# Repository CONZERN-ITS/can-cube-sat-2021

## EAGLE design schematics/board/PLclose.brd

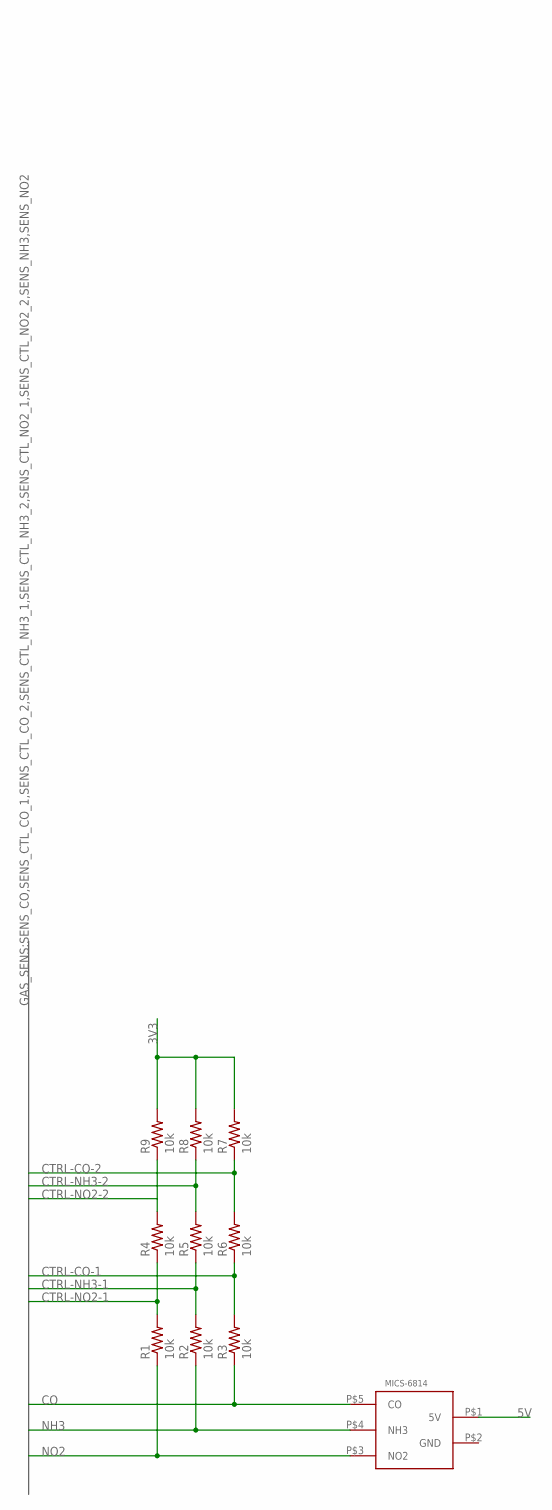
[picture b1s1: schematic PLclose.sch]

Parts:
MICS-6814: MICS-6814
R1, R2, R3, R4, R5, R6, R7, R8, R9: 10k; R0603

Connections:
3V3: R7.2, R8.2, R9.2
5V: MICS-6814.P$1 (5V)
CO: MICS-6814.P$5 (CO), R3.1
CTRL-CO-1: R3.2, R6.1
CTRL-CO-2: R6.2, R7.1
CTRL-NH3-1: R2.2, R5.1
CTRL-NH3-2: R5.2, R8.1
CTRL-NO2-1: R1.2, R4.1
CTRL-NO2-2: R4.2, R9.1
NH3: MICS-6814.P$4 (NH3), R2.1
NO2: MICS-6814.P$3 (NO2), R1.1

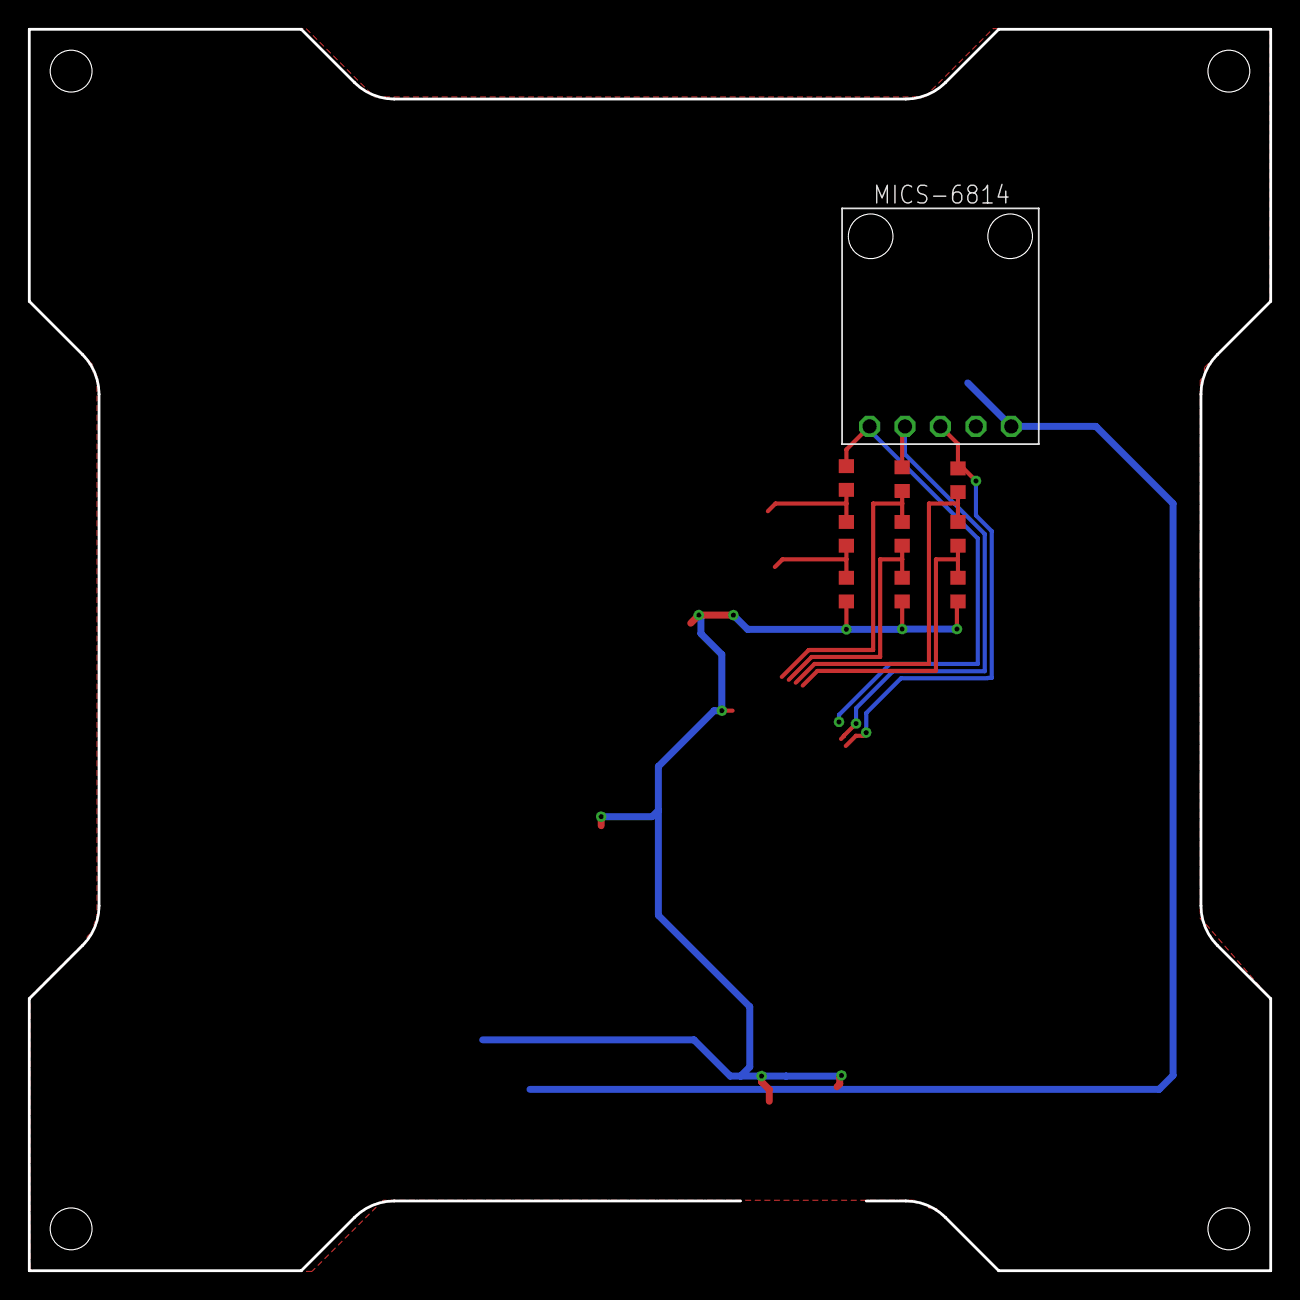
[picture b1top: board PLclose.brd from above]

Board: 2 copper layers, 89.0 x 89.0 mm, 10 parts (0 on the bottom side), 10 nets.

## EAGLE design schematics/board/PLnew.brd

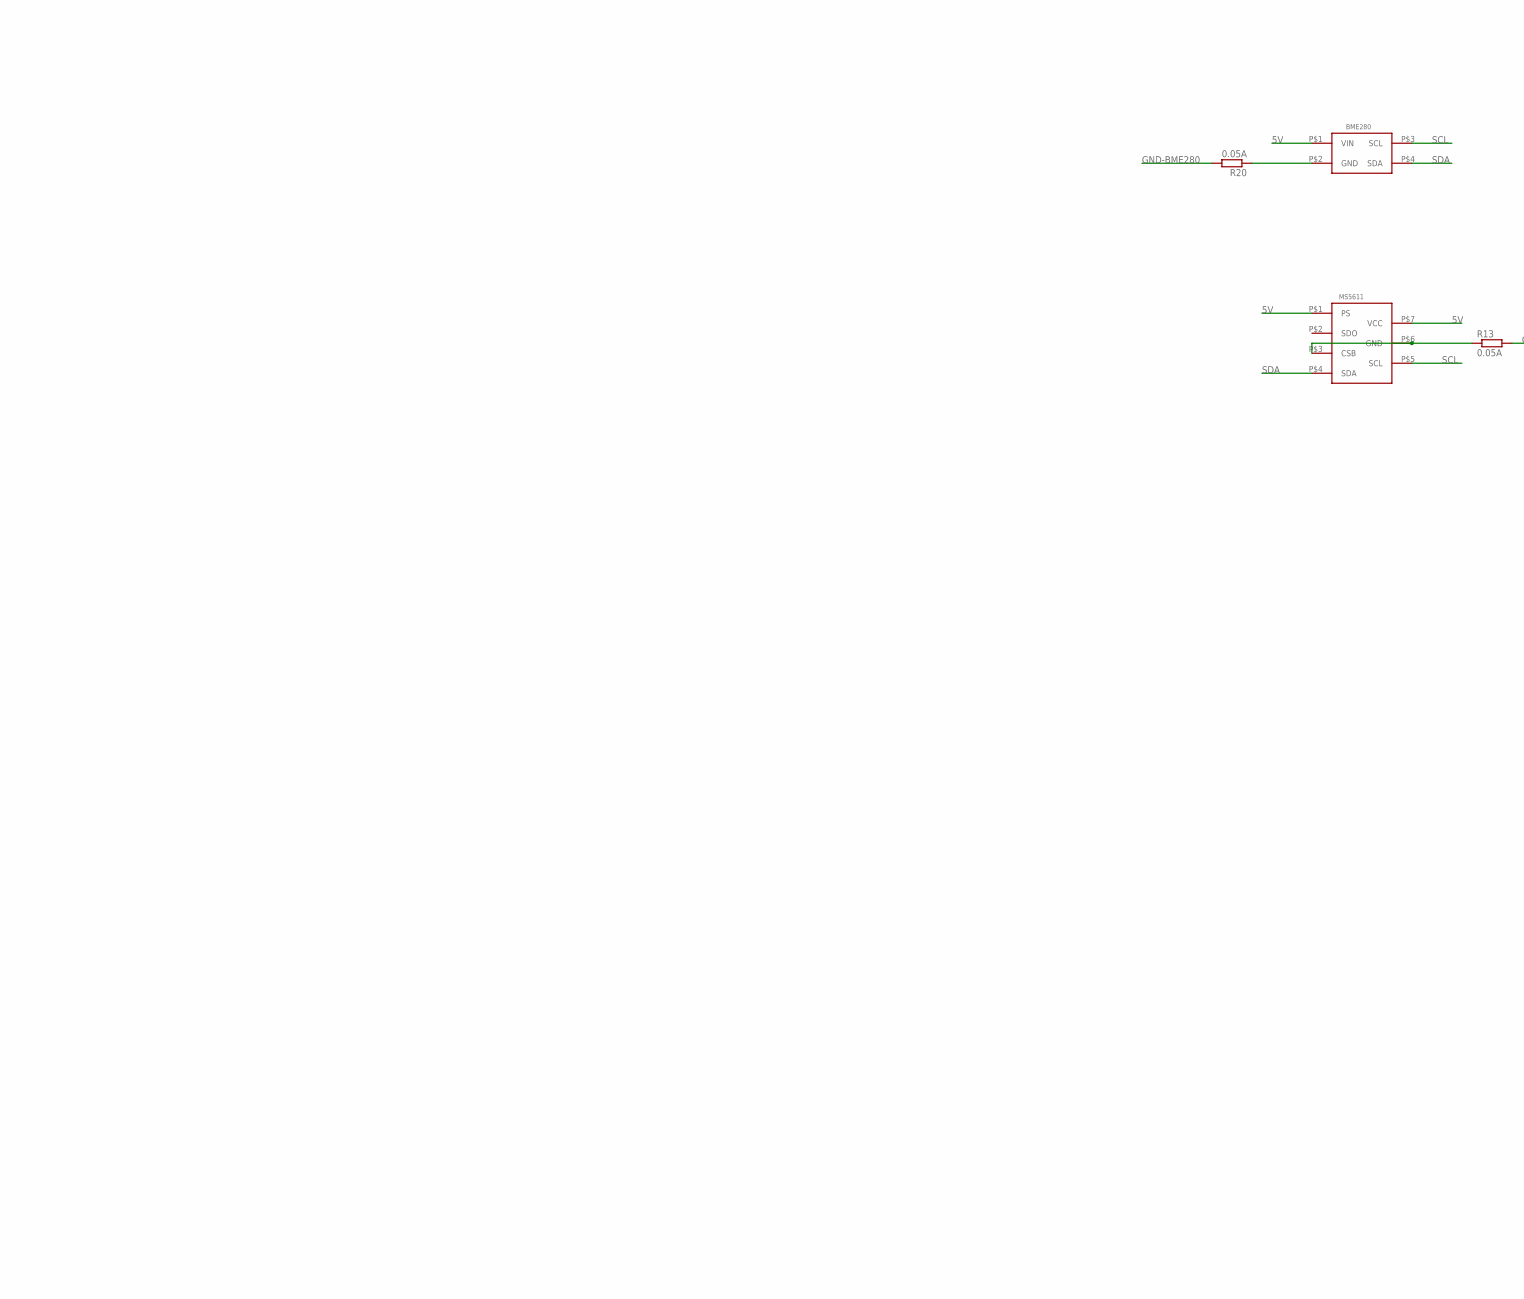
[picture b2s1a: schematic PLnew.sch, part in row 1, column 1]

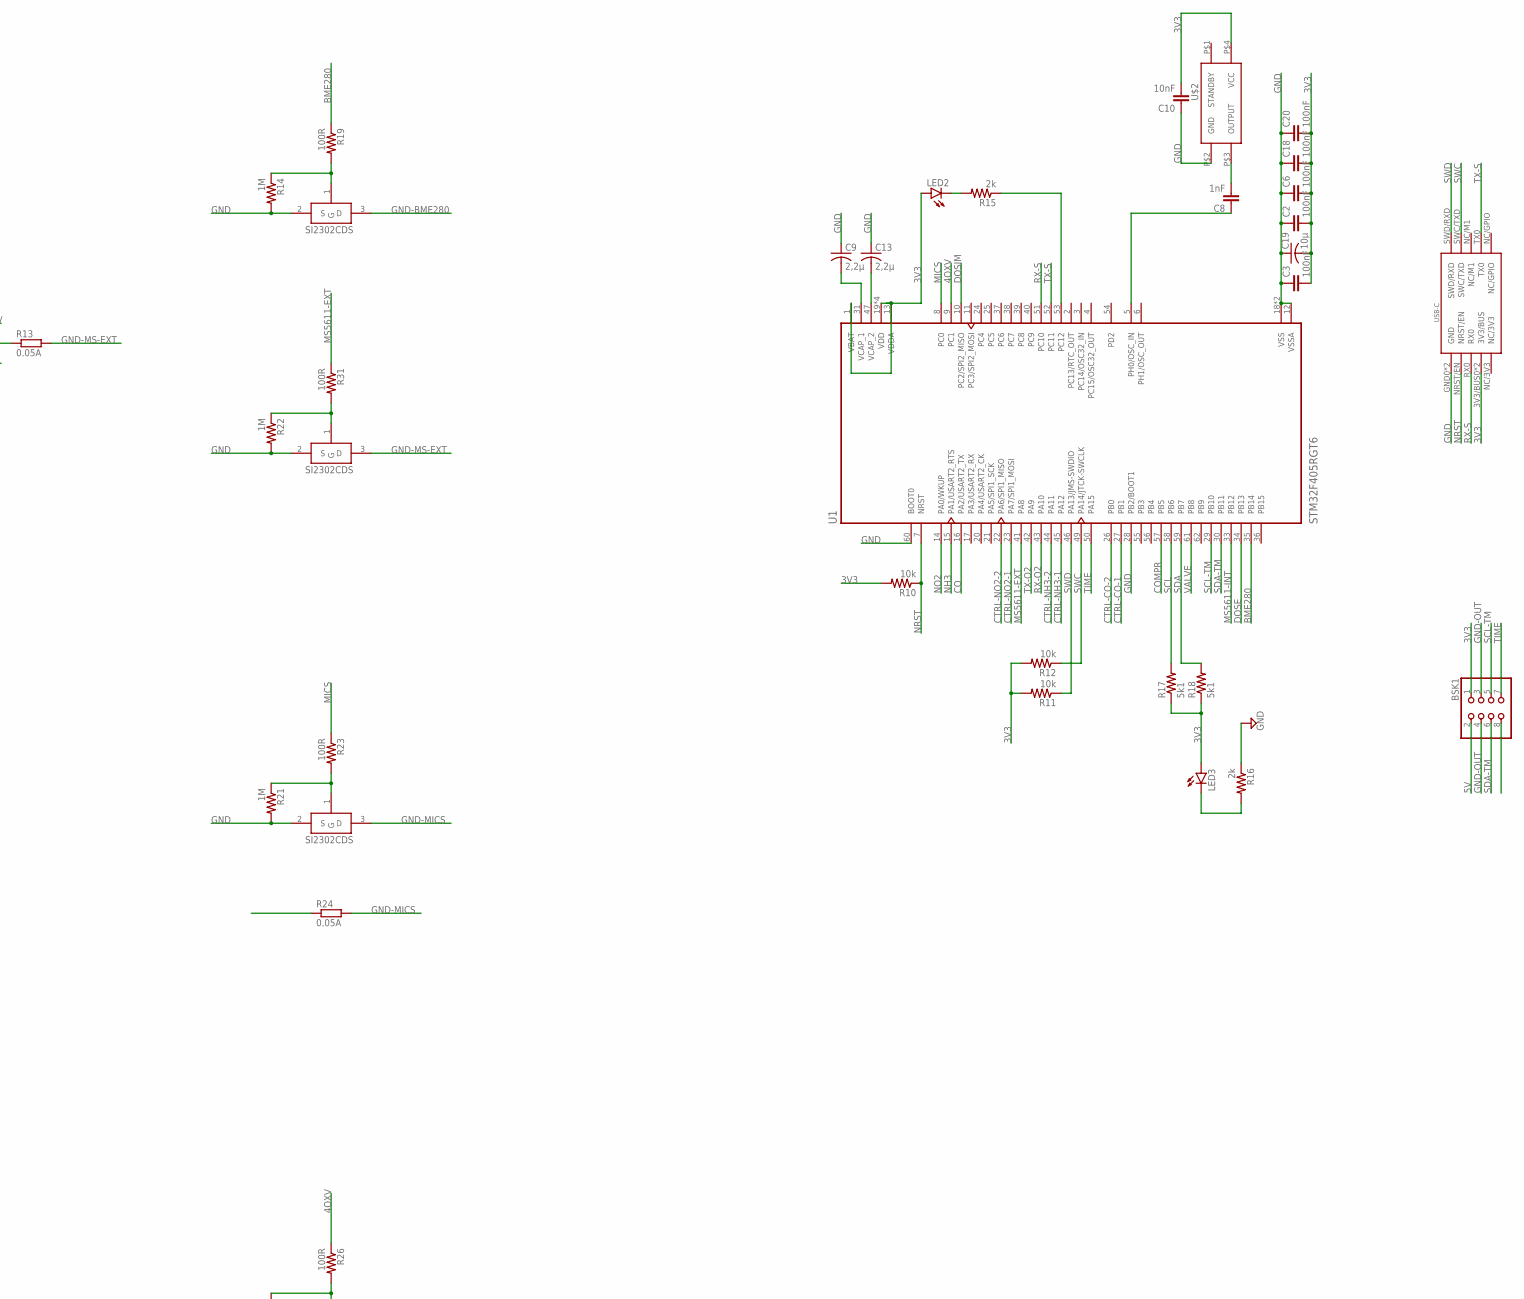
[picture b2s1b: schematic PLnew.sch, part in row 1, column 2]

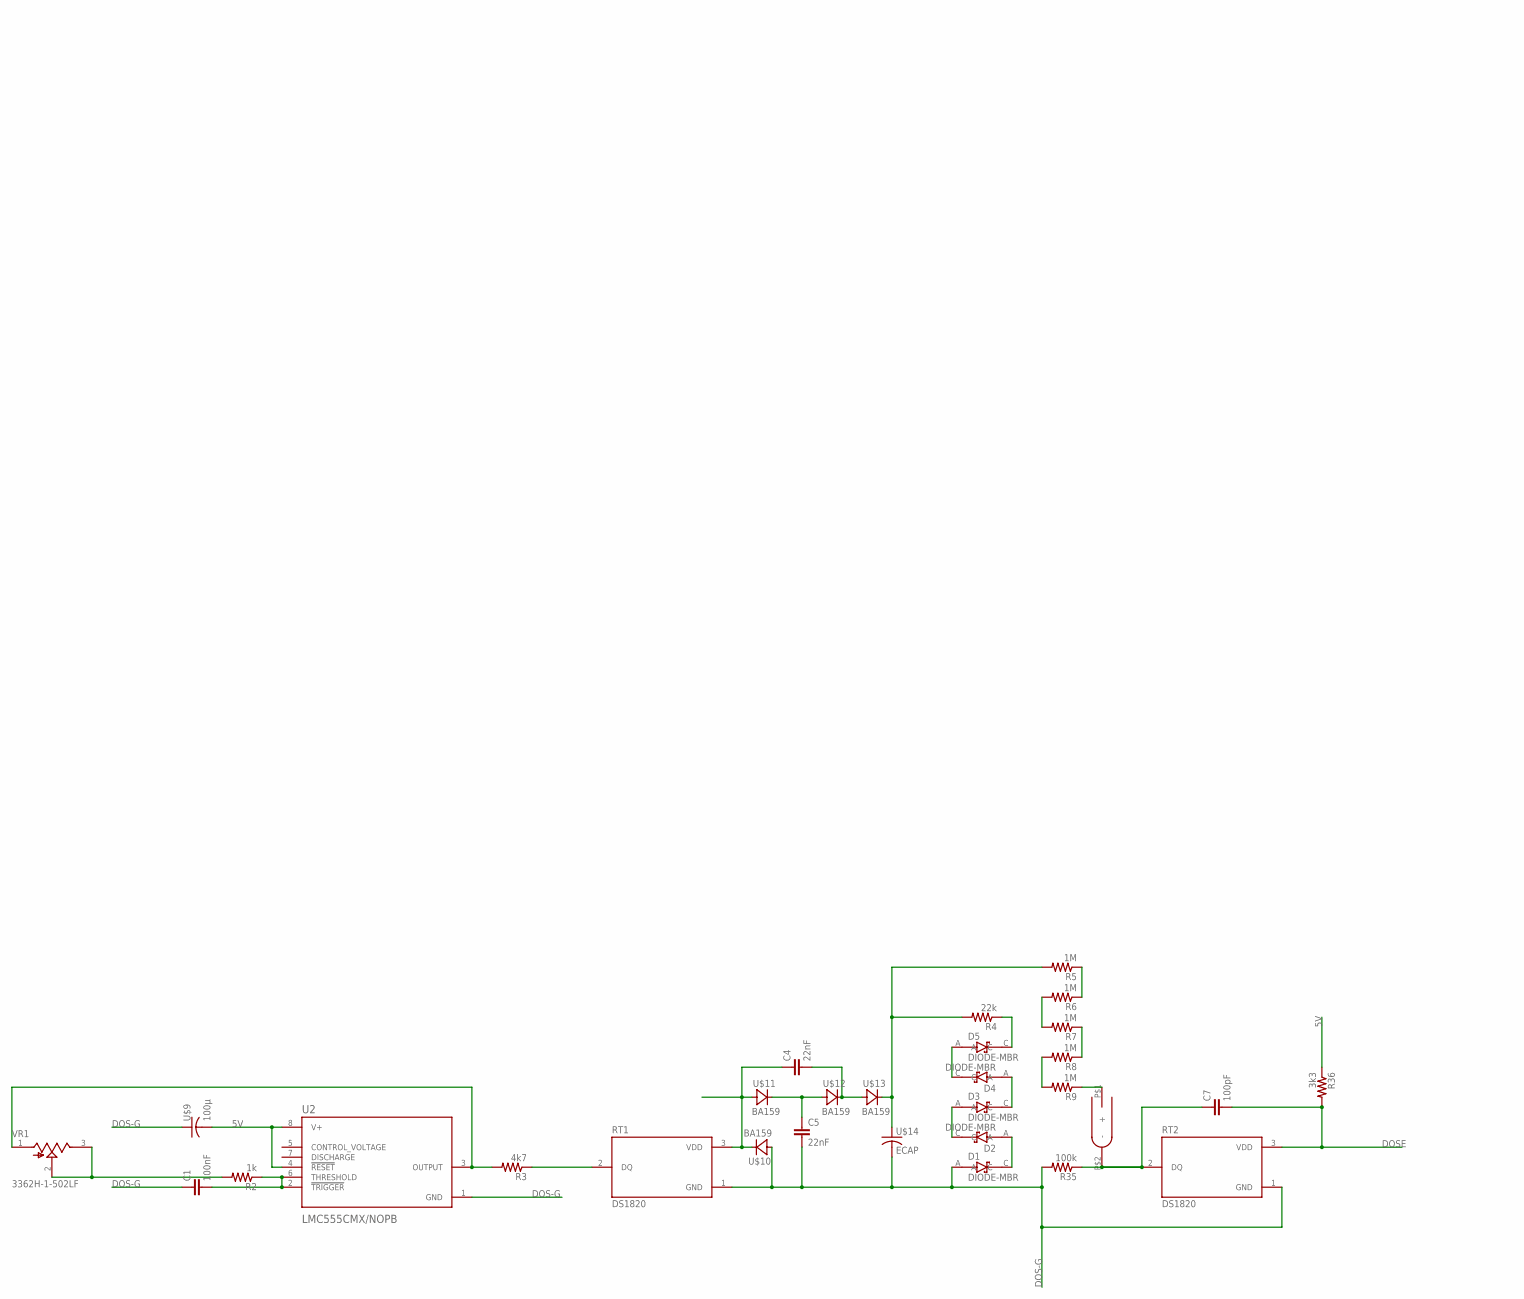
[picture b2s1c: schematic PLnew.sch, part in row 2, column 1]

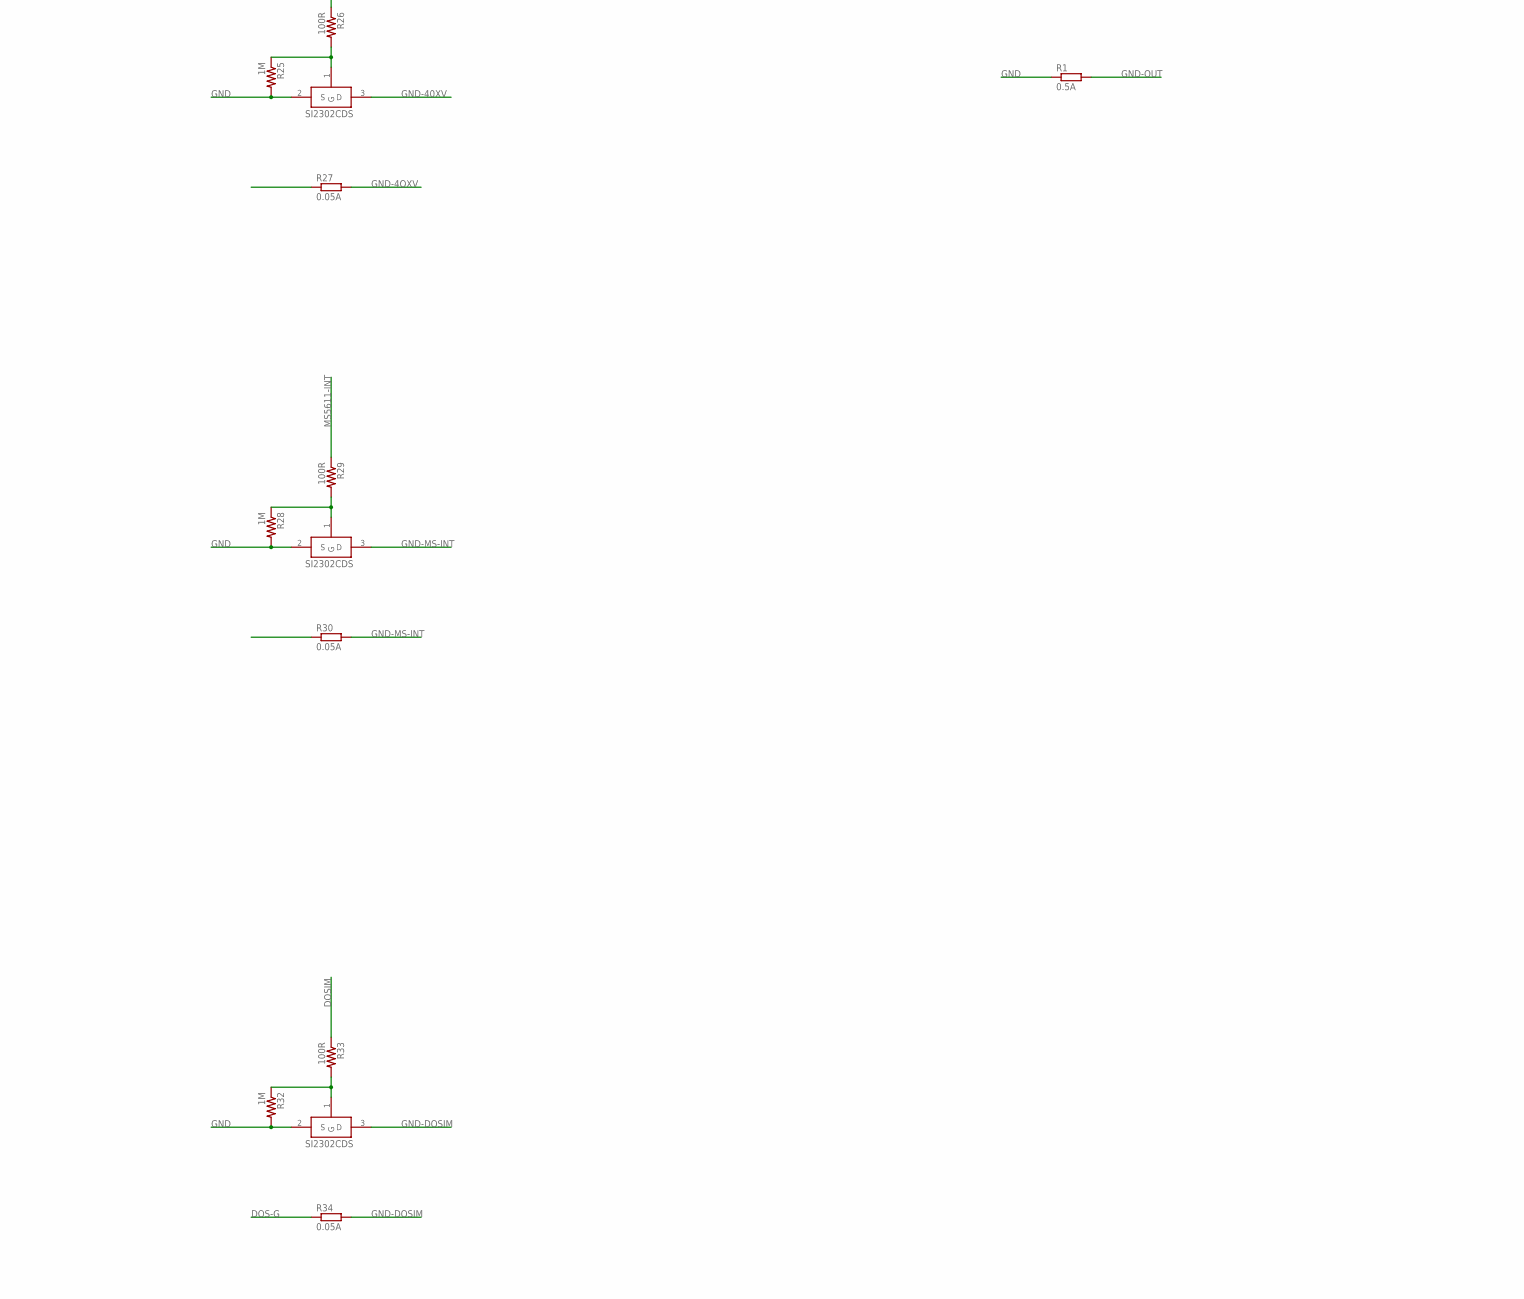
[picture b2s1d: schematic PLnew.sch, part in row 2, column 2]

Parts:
BME280: BME280
BSK1: PINHD-2X4; 2X04
C1, C2, C3, C6, C18, C20: 100nF; C0603
C4, C5: 22nF; C1210
C7: 100pF; C0603
C8: 1nF; C0603
C9, C13: 2,2µ; C0603
C10: 10nF; C0603
C19: 10µ; C1206
D1, D2, D3, D4, D5: DIODE-MBR; SOD123
LED2, LED3: LEDCHIPLED_0603; CHIPLED_0603
R1: 0.5A; R1210
R2: 1k; R0603
R3: 4k7; R0603
R4: 22k; R0603
R5, R6, R7, R8, R9, R14, R21, R22, R25, R28, R32: 1M; R0603
R10, R11, R12: 10k; R0603
R13, R20, R24, R27, R30, R34: 0.05A; R1210
R15, R16: 2k; R0603
R17, R18: 5k1; R0603
R19, R23, R26, R29, R31, R33: 100R; R0603
R35: 100k; R0603
R36: 3k3; R0603
RT1, RT2: DS1820; TO92/TO226
U1: STM32F405RGT6; QFP50P1200X1200X160-64N
U2: LMC555CMX/NOPB; SOIC127P599X175-8N
U$1: MS5611
U$2: Q24
U$3, U$4, U$5, U$7, U$8, U$19: SI2302CDS; SOT23-3
U$6: USB-C
U$9: 100µ; ECAP100-CMD
U$10, U$11, U$12, U$13: BA159
U$14: ECAP; ECAP1MK
U$15: DOSIM
VR1: 3362H-1-502LF; TRIM_3362H-1-502LF

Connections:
3V3: BSK1.1, C2.2, C3.2, C6.2, C10.2, C18.2, C19.2, C20.2, LED2.A, LED3.A, R10.2, R11.2, R12.2, R17.1, R18.1, U1.1 (VBAT), U1.13 (VDDA), U1.19 (VDD), U1.32 (VDD), U1.48 (VDD), U1.64 (VDD), U$2.P$4 (VCC), U$6.3V3/BUS0 (3V3/BUS), U$6.3V3/BUS1 (3V3/BUS)
4OXV: R26.1, U1.9 (PC1)
5V: BME280.P$1 (VIN), BSK1.2, R36.1, U2.4 (!RESET!), U2.8 (V+), U$1.P$1 (PS), U$1.P$7 (VCC), U$9.P$2 (2)
BME280: R19.1, U1.35 (PB14)
CO: U1.16 (PA2/USART2_TX)
COMPR: U1.57 (PB5)
CTRL-CO-1: U1.27 (PB1)
CTRL-CO-2: U1.26 (PB0)
CTRL-NH3-1: U1.45 (PA12)
CTRL-NH3-2: U1.44 (PA11)
CTRL-NO2-1: U1.23 (PA7/SPI1_MOSI)
CTRL-NO2-2: U1.22 (PA6/SPI1_MISO)
DOS-G: C1.1, C5.2, D1.A, R34.1, R35.2, RT1.1 (GND), RT2.1 (GND), U2.1 (GND), U$9.P$1 (1), U$10.P$1 (A), U$14.P$2 (2)
DOSE: C7.2, R36.2, RT2.3 (VDD), U1.34 (PB13)
DOSIM: R33.1, U1.10 (PC2/SPI2_MISO)
GND: C2.1, C3.1, C6.1, C9.1, C10.1, C13.1, C18.1, C19.1, C20.1, R1.1, R14.2, R16.1, R21.2, R22.2, R25.2, R28.2, R32.2, U1.12 (VSSA), U1.18 (VSS), U1.28 (PB2/BOOT1), U1.60 (BOOT0), U1.63 (VSS), U$2.P$2 (GND), U$3.2 (S), U$4.2 (S), U$5.2 (S), U$6.GND0 (GND), U$6.GND1 (GND), U$7.2 (S), U$8.2 (S), U$19.2 (S)
GND-4OXV: R27.2
GND-40XV: U$5.3 (D)
GND-BME280: R20.2, U$3.3 (D)
GND-DOSIM: R34.2, U$8.3 (D)
GND-MICS: R24.2, U$4.3 (D)
GND-MS-EXT: R13.2, U$19.3 (D)
GND-MS-INT: R30.2, U$7.3 (D)
GND-OUT: BSK1.3, BSK1.4, R1.2
MICS: R23.1, U1.8 (PC0)
MS5611-EXT: R31.1, U1.41 (PA8)
MS5611-INT: R29.1, U1.33 (PB12)
unnamed: R13.1, U$1.P$3 (CSB), U$1.P$6 (GND)
unnamed: R14.1, R19.2, U$3.1 (G)
unnamed: BME280.P$2 (GND), R20.1
unnamed: C8.2, U$2.P$3 (OUTPUT)
unnamed: C8.1, U1.5 (PH0/OSC_IN)
unnamed: R21.1, R23.2, U$4.1 (G)
unnamed: R25.1, R26.2, U$5.1 (G)
unnamed: R22.1, R31.2, U$19.1 (G)
unnamed: R28.1, R29.2, U$7.1 (G)
unnamed: R32.1, R33.2, U$8.1 (G)
unnamed: C1.2, R2.1, U2.2 (!TRIGGER!), U2.6 (THRESHOLD)
unnamed: R2.2, VR1.2 (WIPER), VR1.3 (CW)
unnamed: R3.2, U2.3 (OUTPUT), VR1.1 (CCW)
unnamed: R3.1, RT1.2 (DQ)
unnamed: C4.1, RT1.3 (VDD), U$10.P$2 (C), U$11.P$1 (A)
unnamed: C5.1, U$11.P$2 (C), U$12.P$1 (A)
unnamed: C4.2, U$12.P$2 (C), U$13.P$1 (A)
unnamed: R4.2, R5.2, U$13.P$2 (C), U$14.P$1 (1)
unnamed: D1.C, D2.A
unnamed: D2.C, D3.A
unnamed: D3.C, D4.A
unnamed: D4.C, D5.A
unnamed: D5.C, R4.1
unnamed: R5.1, R6.1
unnamed: C13.2, U1.47 (VCAP_2)
unnamed: R6.2, R7.2
unnamed: R7.1, R8.1
unnamed: R8.2, R9.2
unnamed: R9.1, U$15.P$1 (+)
unnamed: C7.1, R35.1, RT2.2 (DQ), U$15.P$2 (-)
unnamed: C9.2, U1.31 (VCAP_1)
unnamed: LED2.C, R15.2
unnamed: R15.1, U1.53 (PC12)
unnamed: LED3.C, R16.2
NH3: U1.15 (PA1/USART2_RTS)
NO2: U1.14 (PA0/WKUP)
NRST: R10.1, U1.7 (NRST), U$6.NRST/EN
RX-O2: U1.43 (PA10)
RX-S: U1.51 (PC10), U$6.RX0
SCL: BME280.P$3 (SCL), R17.2, U1.58 (PB6), U$1.P$5 (SCL)
SCL-TM: BSK1.5, U1.29 (PB10)
SDA: BME280.P$4 (SDA), R18.2, U1.59 (PB7), U$1.P$4 (SDA)
SDA-TM: BSK1.6, U1.30 (PB11)
SWC: R12.1, U1.49 (PA14/JTCK-SWCLK), U$6.SWC/TXD
SWD: R11.1, U1.46 (PA13/JMS-SWDIO), U$6.SWD/RXD
TIME: BSK1.7, U1.50 (PA15)
TX-O2: U1.42 (PA9)
TX-S: U1.52 (PC11), U$6.TX0
VALVE: U1.61 (PB8)

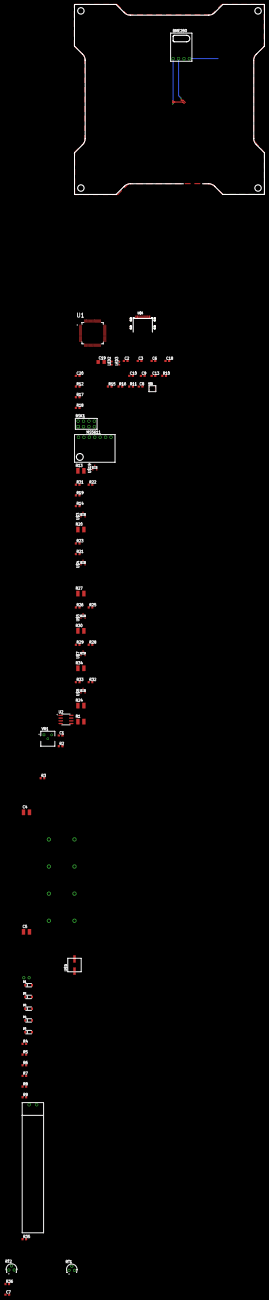
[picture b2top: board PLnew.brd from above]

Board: 2 copper layers, 80 parts (0 on the bottom side), 61 nets.

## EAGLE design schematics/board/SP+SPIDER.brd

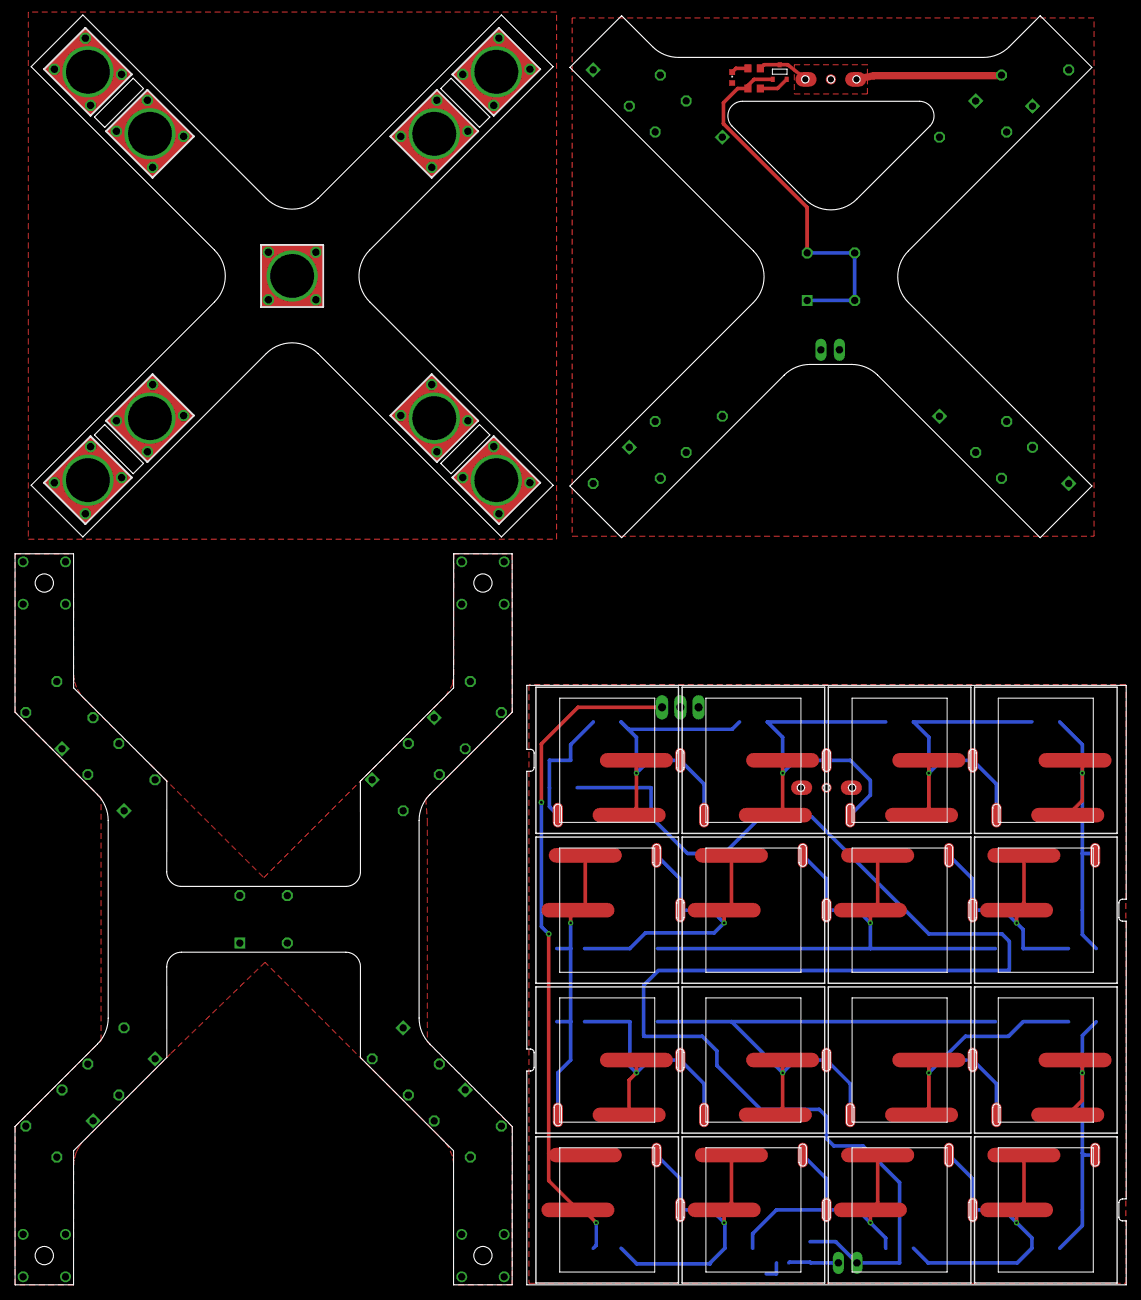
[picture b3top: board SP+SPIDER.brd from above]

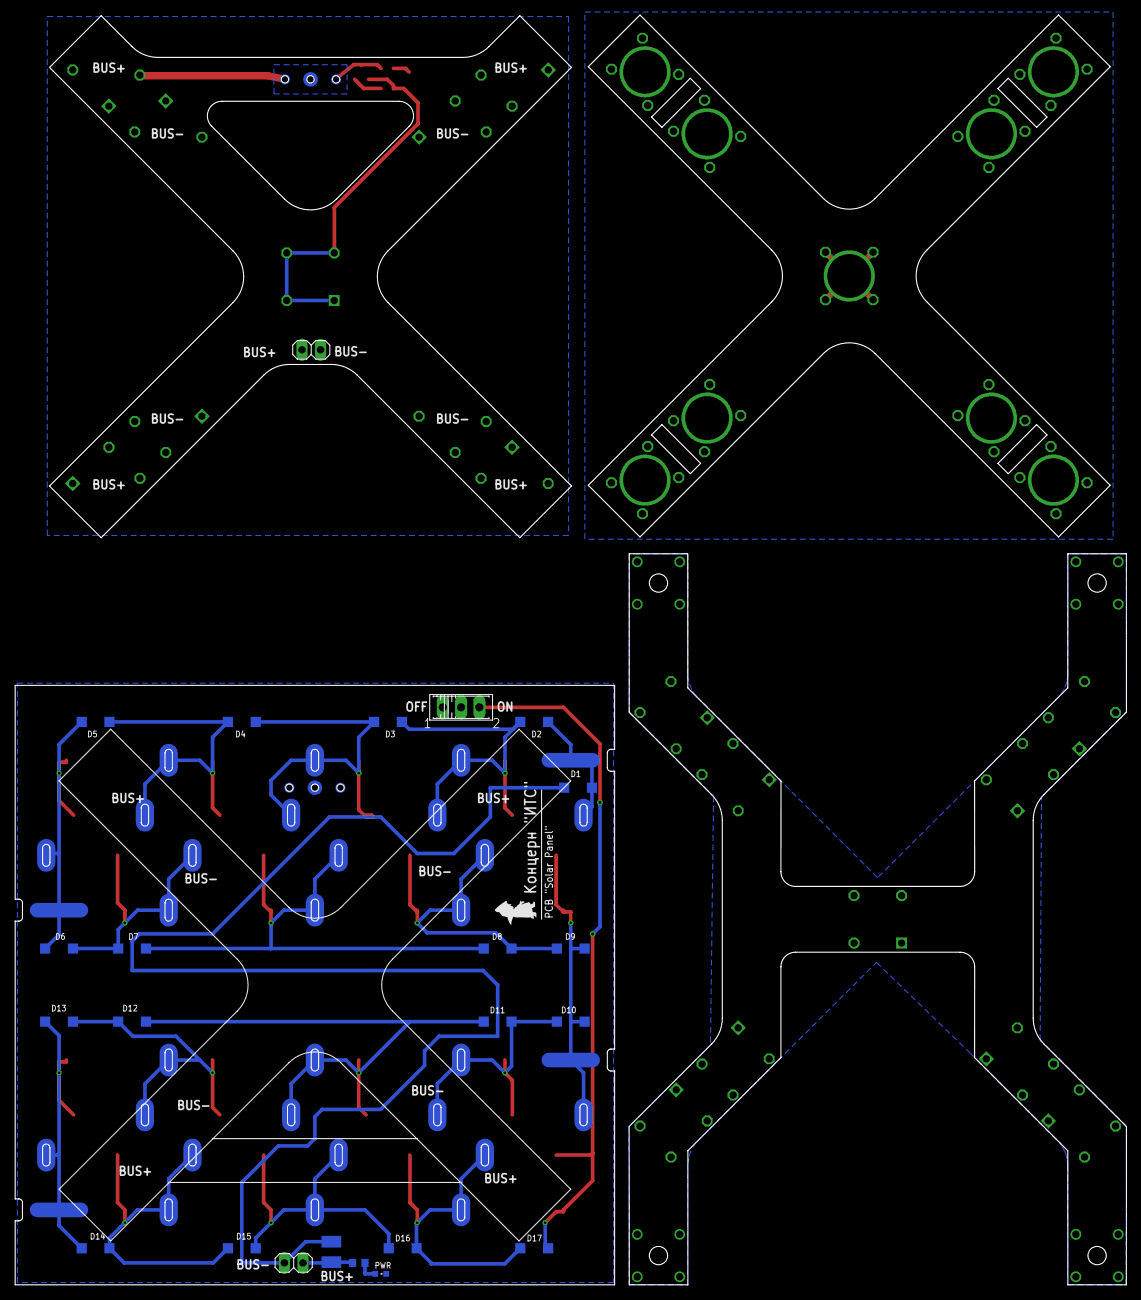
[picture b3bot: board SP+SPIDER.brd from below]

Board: 2 copper layers, 152.0 x 173.7 mm, 73 parts (32 on the bottom side), 32 nets.

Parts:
2K7: 2k7; R0603
C1: 47µ; C1210
D1, D2, D3, D4, D5, D6, D7, D8, D9, D10, D11, D12, D13, D14, D15, D16, D17: MBR0520LT; SOD123
JP1, JP3: 1X02
LED1: CHIPLED_0603
PWR: CHIPLED_0603
R1: 1k5; R0603
R2: 1M; R0603
S1: 255SB
SOL1, SOL2, SOL3, SOL5, SOL6, SOL7, SOL9, SOL10, SOL11, SOL13, SOL14, SOL15: SOLAR-2_0; SOLAR_0-2
SOL4, SOL8, SOL12, SOL16: SOLAR-2_1; SOLAR_1-2
U$1, U$2, U$3, U$4, U$18, U$19, U$20, U$21: KCONNECT-
U$5, U$42: KCONNECTQUAD-; KCONNECT-_QUAD
U$6, U$41: GRAFITGRAFIT4_2; GRAFIT4_2
U$7: PCB "Solar Panel"; ITS-LOGO
U$17, U$22, U$23, U$24, U$25, U$26, U$27, U$28: KCONNECT
U$29: KCONNECTQUAD; KCONNECT_QUAD
U$32, U$33, U$38, U$39: KCONNECT3; KCONNECT-3
U$34, U$35, U$36: KCONNECT4; KCONNECT-4
U$37: KCONNECT1; KCONNECT-1
U$40: SI2302CDS; SOT23-3

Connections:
1: R1.2, U$40.3, U$41.P$1, U$41.P$4
BUS+: U$1.1, U$1.2, U$1.3, U$1.4, U$3.1, U$3.2, U$3.3, U$3.4, U$18.1, U$18.2, U$18.3, U$18.4, U$20.1, U$20.2, U$20.3, U$20.4
BUS+1: 2K7.1, C1.2, JP1.2, S1.2
BUS+2: U$17.1, U$17.2, U$17.3, U$17.4, U$17.P$1, U$17.P$2, U$22.1, U$22.2, U$22.3, U$22.4, U$22.P$1, U$22.P$2, U$25.1, U$25.2, U$25.3, U$25.4, U$25.P$1, U$25.P$2, U$27.1, U$27.2, U$27.3, U$27.4, U$27.P$1, U$27.P$2
BUS+4: JP3.2, LED1.A, U$32.1, U$32.2, U$32.4, U$34.1, U$34.2, U$34.3, U$36.1, U$36.2, U$36.3, U$38.1, U$38.2, U$38.4, U$41.P$2, U$41.P$5
BUS-: U$2.1, U$2.2, U$2.3, U$2.4, U$4.1, U$4.2, U$4.3, U$4.4, U$19.1, U$19.2, U$19.3, U$19.4, U$21.1, U$21.2, U$21.3, U$21.4
BUS-1: C1.1, D1.C, JP1.1, PWR.C
BUS-3: JP3.1, U$33.1, U$33.2, U$33.4, U$35.1, U$35.2, U$35.3, U$37.2, U$37.3, U$37.4, U$39.1, U$39.2, U$39.4
CMD: U$5.1, U$5.2, U$5.3, U$5.4
CMD1: U$29.1, U$29.2, U$29.3, U$29.4, U$29.P$1, U$29.P$2
GND1: R2.2, U$40.2
unnamed: D17.A, S1.3, SOL1.IN, SOL1.IN-2
unnamed: U$23.1, U$23.2, U$23.3, U$23.4, U$23.P$1, U$23.P$2, U$24.1, U$24.2, U$24.3, U$24.4, U$24.P$1, U$24.P$2, U$26.1, U$26.2, U$26.3, U$26.4, U$26.P$1, U$26.P$2, U$28.1, U$28.2, U$28.3, U$28.4, U$28.P$1, U$28.P$2
unnamed: D16.A, D17.C, SOL1.OUT, SOL1.OUT1, SOL1.OUT-2, SOL1.OUT-21, SOL2.IN, SOL2.IN-2
unnamed: D15.A, D16.C, SOL2.OUT, SOL2.OUT1, SOL2.OUT-2, SOL2.OUT-21, SOL3.IN, SOL3.IN-2
unnamed: D14.A, D15.C, SOL3.OUT, SOL3.OUT1, SOL3.OUT-2, SOL3.OUT-21, SOL4.IN, SOL4.IN-2
unnamed: D12.A, D13.C, SOL5.OUT, SOL5.OUT1, SOL5.OUT-2, SOL5.OUT-21, SOL6.IN, SOL6.IN-2
unnamed: D11.A, D12.C, SOL6.OUT, SOL6.OUT1, SOL6.OUT-2, SOL6.OUT-21, SOL7.IN, SOL7.IN-2
unnamed: D13.A, D14.C, SOL4.OUT, SOL4.OUT-2, SOL4.OUT-21, SOL5.IN, SOL5.IN-2
unnamed: D10.A, D11.C, SOL7.OUT, SOL7.OUT1, SOL7.OUT-2, SOL7.OUT-21, SOL8.IN, SOL8.IN-2
unnamed: D9.A, D10.C, SOL8.OUT, SOL8.OUT-2, SOL8.OUT-21, SOL9.IN, SOL9.IN-2
unnamed: D8.A, D9.C, SOL9.OUT, SOL9.OUT1, SOL9.OUT-2, SOL9.OUT-21, SOL10.IN, SOL10.IN-2
unnamed: D7.A, D8.C, SOL10.OUT, SOL10.OUT1, SOL10.OUT-2, SOL10.OUT-21, SOL11.IN, SOL11.IN-2
unnamed: D6.A, D7.C, SOL11.OUT, SOL11.OUT1, SOL11.OUT-2, SOL11.OUT-21, SOL12.IN, SOL12.IN-2
unnamed: D5.A, D6.C, SOL12.OUT, SOL12.OUT-2, SOL12.OUT-21, SOL13.IN, SOL13.IN-2
unnamed: D4.A, D5.C, SOL13.OUT, SOL13.OUT1, SOL13.OUT-2, SOL13.OUT-21, SOL14.IN, SOL14.IN-2
unnamed: D3.A, D4.C, SOL14.OUT, SOL14.OUT1, SOL14.OUT-2, SOL14.OUT-21, SOL15.IN, SOL15.IN-2
unnamed: D2.A, D3.C, SOL15.OUT, SOL15.OUT1, SOL15.OUT-2, SOL15.OUT-21, SOL16.IN, SOL16.IN-2
unnamed: D1.A, D2.C, SOL16.OUT, SOL16.OUT-2, SOL16.OUT-21
unnamed: 2K7.2, PWR.A
unnamed: LED1.C, R1.1
ROZE1: R2.1, U$40.1, U$42.1, U$42.2, U$42.3, U$42.4

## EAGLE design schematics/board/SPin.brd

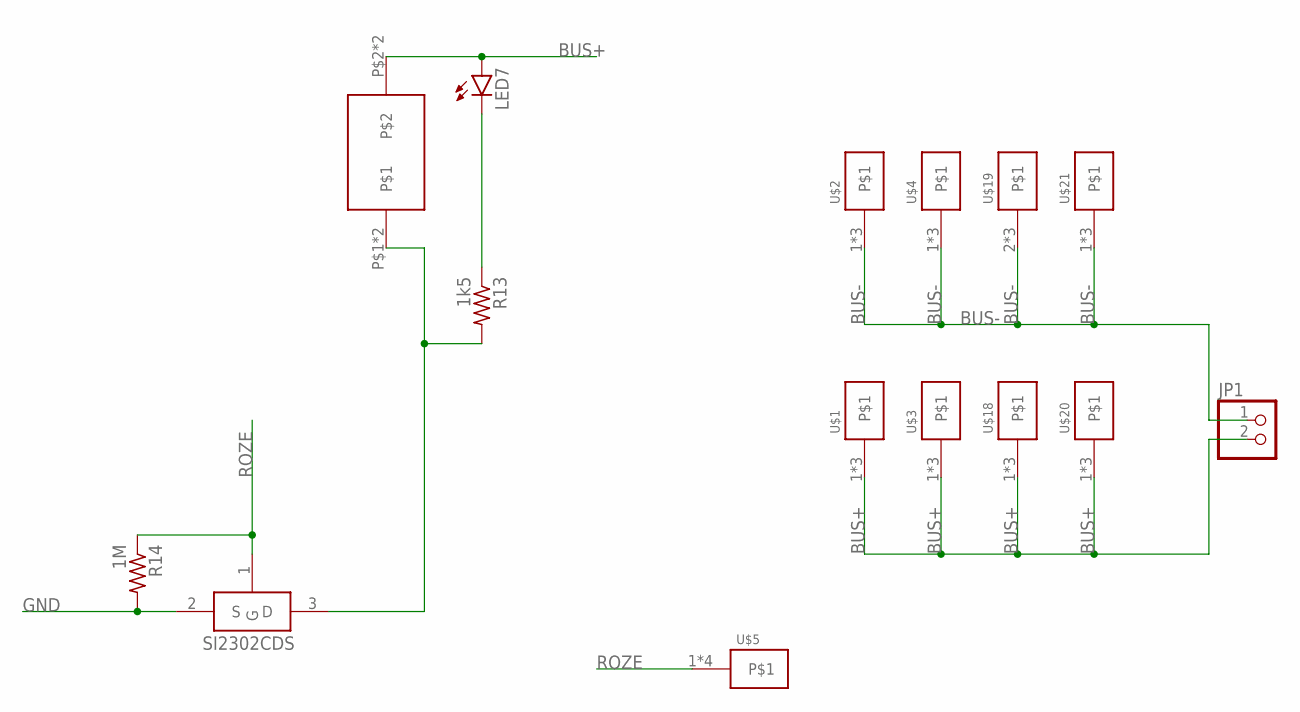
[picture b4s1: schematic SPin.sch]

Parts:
JP1: PINHD-1X2; 1X02
LED7: LEDCHIPLED_0603; CHIPLED_0603
R13: 1k5; R0603
R14: 1M; R0603
U$1, U$2, U$20, U$21: KCONNECT3; KCONNECT-3
U$3, U$4, U$18: KCONNECT4; KCONNECT-4
U$5: KCONNECTQUAD-; KCONNECT-_QUAD
U$6: GRAFITGRAFIT4_2; GRAFIT4_2
U$13: SI2302CDS; SOT23-3
U$19: KCONNECT1; KCONNECT-1

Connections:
2: R13.2, U$6.P$1, U$6.P$4, U$13.3 (D)
BUS+: JP1.2, LED7.A, U$1.1, U$1.2, U$1.4, U$3.1, U$3.2, U$3.3, U$6.P$2, U$6.P$5, U$18.1, U$18.2, U$18.3, U$20.1, U$20.2, U$20.4
BUS-: JP1.1, U$2.1, U$2.2, U$2.4, U$4.1, U$4.2, U$4.3, U$19.2, U$19.3, U$19.4, U$21.1, U$21.2, U$21.4
GND: R14.2, U$13.2 (S)
unnamed: LED7.C, R13.1
ROZE: R14.1, U$5.1, U$5.2, U$5.3, U$5.4, U$13.1 (G)

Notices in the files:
parts and their libraries:
SparkFun-Capacitors: Licensing: Creative Commons ShareAlike 4.0 International - https://creativecommons.org/licenses/by-sa/4.0
microbuilder: This work is placed in the public domain, and may be freely used for commercial and non-commercial work with the following conditions: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
